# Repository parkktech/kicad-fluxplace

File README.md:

# fluxplace

Signal-flow-aware placement, routing analysis, design review and fab packaging for KiCad 10.
Reads a board's communication graph, places by connection, gates routing on a pre-route
scorecard, then reviews, packages. One pcbnew-free core; a headless CLI, a KiCad plugin
and an MCP server. Built on the RAZOR-01 CM5 carrier (178 parts): about 50% less weighted
wirelength, 28% less area.

**AI agents: read only [AGENTS.md](AGENTS.md).** Per-command detail: `fluxplace help-brief CMD`.

## Install

    pip install -e .            # numpy only; pcbnew comes from KiCad's own python
    fluxplace doctor            # names every missing dependency (KiCad, router, API keys)

Requirements, the interpreter trap (pcbnew needs KiCad's python), toolchain:
[docs/INSTALL.md](docs/INSTALL.md).

## Pipeline

`fluxplace pipeline BOARD --constraints C --spec S --workdir W` runs seven stages, each reading only the
previous board and `W/state.json`, so each can run in its own agent context:
floorplan-check, anchor-check, place (clusters, routable), route-ready gate, route (fanout, time-boxed,
stall loop; `route-wait` instead of log polling), tune, review. `--from/--to/--status` select and inspect.
Subagent briefs: [docs/AGENT-PIPELINE.md](docs/AGENT-PIPELINE.md).

Analysis commands print a compact report (verdict, counts, worst N, path);
`--full` restores everything, `-q` verdict only ([docs/commands/output.md](docs/commands/output.md)).

## Commands

Details: `fluxplace help-brief CMD` or [docs/commands/](docs/commands/).

<!-- index:start -->
deliver           split a fab package: CAM-only zip + loose...
pcbway            PCBWay order worksheet: every field on the...
sourcing          grade every MPN against live...
analyze           print the communication map: hub...
place             re-place components (--strategy...
plan              gather info + write a detailed placement...
gather            dump structured board facts as JSON
route             global-route the current placement, report...
fit-sheet         translate the whole board onto the drawing...
title-block       fill the drawing-sheet title block (title...
tournament        N placements -> gate filter -> freerouting...
fab               emit gerbers/drill/place/DRC package for...
comprehend-intent infer electrical intent as TOML: pairs...
preflight         parse-level sanity: outline, pads...
patch             close leftover unrouted nets on a routed...
launder           set board constraints to the fab profile...
verify-models     verify 3D models sit ON their...
sync-nets         make board pad nets agree with the...
replace-footprint swap a ref's footprint for a real library...
auto              board in -> place -> route -> fab package...
compact           shrink a known-good placement -> route ->...
lint              design-completeness checks: missing...
datasheets        fetch every MPN's datasheet into the...
spec-check        documentation gate on a netlist spec...
lock              print a [lock.at] constraints block for...
bom-opt           part-count optimization: array...
route-diagnose    read-only: explain why nets stayed...
anchor-check      evaluate every allowed rotation of each...
route-ready       pre-route gate: net budgets, support...
map               meta map: compact JSON of parts, groups...
plan-route        escape planner + global router on the...
plan-options      what-if recommender: the smallest...
plan-compare      two maps' plan verdicts side by side
density           courtyard + fan-out ring utilisation per...
fanout            real, locked escape copper for every pin...
modules           group ICs/connectors with their support...
floorplan         place modules as rigid blocks (construct +...
snap-vias         track ends in a via go to its centre
closure           open connections: pocket, walls, via sites...
pairs             lay the differential pairs by construction...
join-gaps         close small same-net copper gaps (track...
intent            INTENT gate: every placement-intent item...
intent-draft      propose an [intent] section from the board...
wl-refine         shorten wire length
parts             part-entry gate...
ready             readiness gate before place/route: parts...
pin-groups        functional pin groups of multi-channel...
part-diff         substitution diff: old vs new part pin...
clusters          IC support clusters (which 2-pin parts...
floorplan-check   area budget before placing: per block and...
templates         place [placement.template.NAME] structure...
silk              silkscreen check (off board, over...
magnetics         LAN magnetics wiring check vs datasheet pins
review            design-review gate: spec net rules...
repair            copper repairs the review gate asks for...
finish            route named nets with freerouting and take...
drc-fix           fix the DRC noise a repair leaves behind...
tune              DRC-guarded diff-pair length tuning...
models            fetch real vendor STEP models...
intake            design interview: connectors (edge/remote...
calibrate         ground-truth the gate vs freerouting (DSN...
eval              placement quality: weighted wirelength...
comprehend        auto-detect physics constraints (power...
doctor            preflight: check KiCad, python deps...
drc-scope         what a DRC result actually examined —...
netlist           read the connection list back out of the...
stackup           layer stack, plane assignment, netclass...
stackup-define    define the board stackup from a fab...
schematic         generate a .kicad_sch from a netlist spec...
route-status      one line from a router run's...
route-wait        block until the router is...
pipeline          staged pipeline, one stage per agent...
help-brief        at most 15 lines on one command (none: one...
<!-- index:end -->

## More

[CLI reference](docs/commands/cli.md), [docs/INTENT.md](docs/INTENT.md), [docs/ARCHITECTURE.md](docs/ARCHITECTURE.md),
[docs/CHANGELOG.md](docs/CHANGELOG.md), [NEXT.md](NEXT.md), [Cypress engine](docs/CYPRESS.md).

MIT (c) 2026 Jason Ratzlaff

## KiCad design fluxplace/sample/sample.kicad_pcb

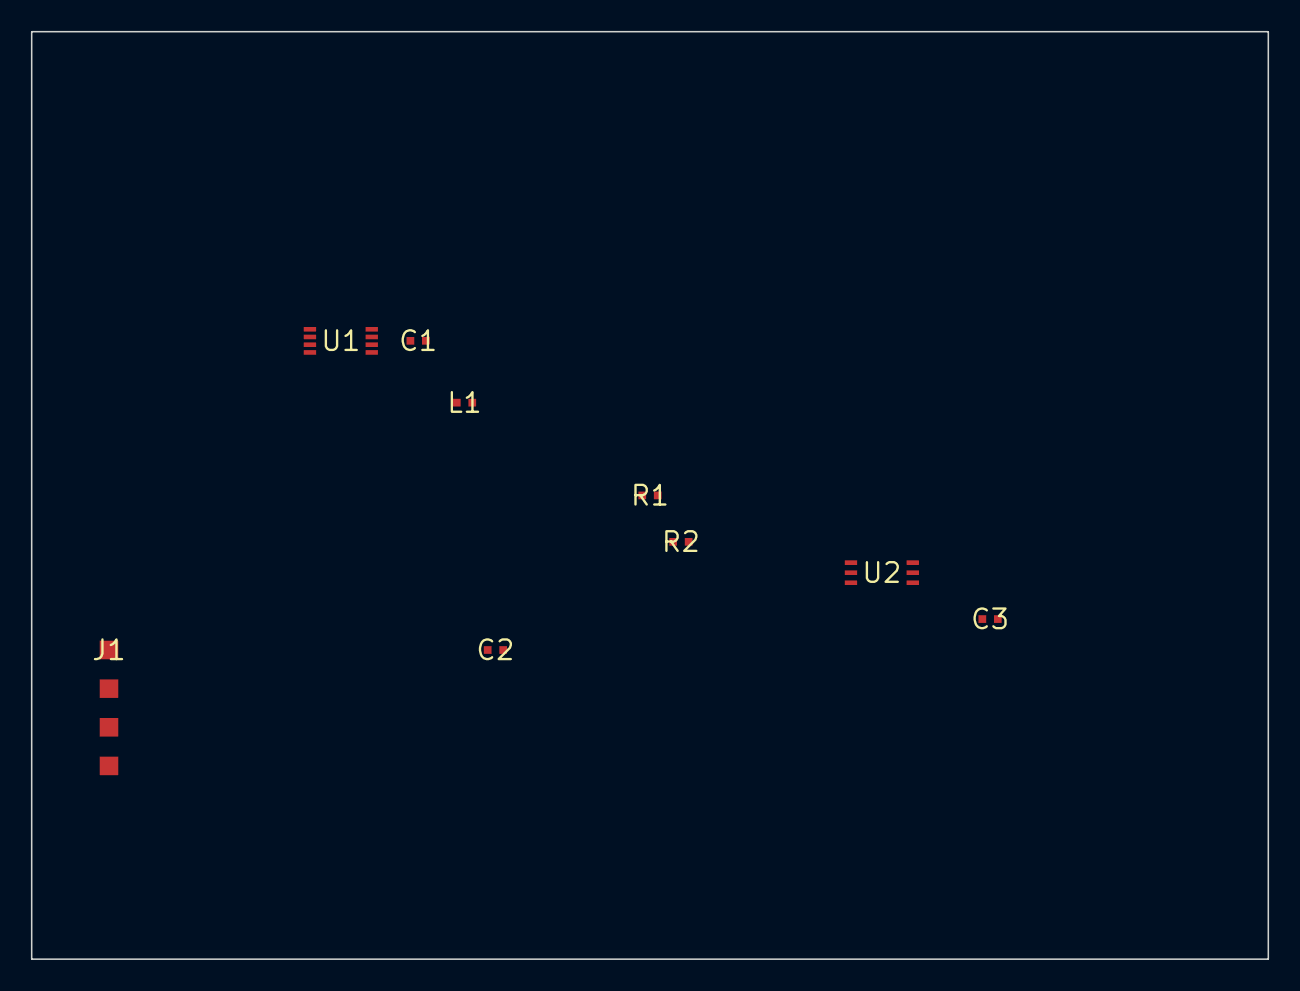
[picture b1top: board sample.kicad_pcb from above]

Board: 4 copper layers, 80.0 x 60.0 mm, 9 parts (0 on the bottom side), 8 nets, no tracks yet.

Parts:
C1: C1; R_0402
C2: C2; R_0402
C3: C3; R_0402
J1: J1; Header_1x4_Sample
L1: L1; R_0402
R1: R1; R_0402
R2: R2; R_0402
U1: U1; QFN-8_Sample
U2: U2; SOT-6_Sample

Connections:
GND: C1.2, C2.2, J1.2, U1.7, U2.6
RF_IN: C3.1, U2.3
RF_OUT: C3.2, U2.4
SCL: J1.3, R1.1, U1.5, U2.1
SDA: J1.4, R2.1, U1.6, U2.2
SW: L1.1, U1.3
VIN: C1.1, J1.1, U1.1
VOUT: C2.1, L1.2, R1.2, R2.2, U1.8, U2.5
